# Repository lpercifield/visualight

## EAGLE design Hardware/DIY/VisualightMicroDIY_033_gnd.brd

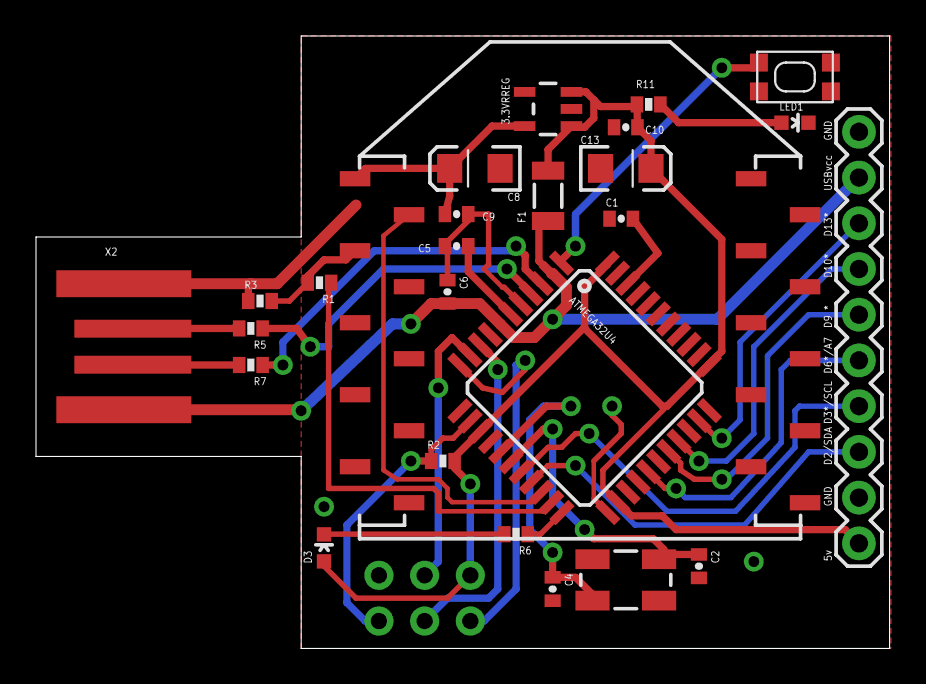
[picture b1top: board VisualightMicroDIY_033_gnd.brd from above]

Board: 2 copper layers, 47.4 x 34.0 mm, 27 parts (1 on the bottom side), 29 nets.

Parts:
3.3VRREG: MIC5219 3.3V; SOT23-5
ATMEGA32U4: ATMEGA32U4; SPARKFUN-DIGITALIC_TQFP44
C1, C9: 0.1uF; 0402-CAP
C2, C4: 22pF; 0402-CAP
C5, C6, C10: 1uF; 0402-CAP
C8, C13: 10uF; EIA3216
D3: Green; LED-0603
F1: 500mA; PTC-1206
ISP1: AVRISP-6; AVRISP
JP1: M10"; 1X10
LED1: Red; LED-0603
R1: 2.2K; 0402-RES
R2: 10K; 0402-RES
R3: 3.3K; 0402-RES
R5, R7: 22; 0402-RES
R6: 330; 0402-RES
R11: 1K; 0402-RES
SW1: SPST_TACT-KMR2; KMR2
U$1: XBEE-1B3; XBEE-SMD
X2: USBPCB; USB-A-PCB
Y1: 16MHz; CRYSTAL-SMD-5X3

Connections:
+3V3_OUT: 3.3VRREG.5, C8.A, C9.2, U$1.1
AREF: ATMEGA32U4.42, C1.2
D2: ATMEGA32U4.19, JP1.3
D3: ATMEGA32U4.18, JP1.4
D6: ATMEGA32U4.27, JP1.5
D7: ATMEGA32U4.1, SW1.3
D9: ATMEGA32U4.29, JP1.6
D10: ATMEGA32U4.30, JP1.7
D13: ATMEGA32U4.32, JP1.8
D+: ATMEGA32U4.4, R5.1
D-: ATMEGA32U4.3, R7.1
GND: 3.3VRREG.2, ATMEGA32U4.5, ATMEGA32U4.15, ATMEGA32U4.23, ATMEGA32U4.33, ATMEGA32U4.35, ATMEGA32U4.43, C1.1, C2.2, C4.2, C5.1, C6.1, C8.C, C9.1, C10.2, C13.C, ISP1.6, JP1.2, JP1.10, LED1.C, R3.1, SW1.4, U$1.10, X2.GND
MISO: ATMEGA32U4.11, ISP1.1
MOSI: ATMEGA32U4.10, ISP1.4
unnamed: ATMEGA32U4.16, C4.1, Y1.1
unnamed: ATMEGA32U4.17, C2.1, Y1.3
unnamed: ATMEGA32U4.6, C5.2
unnamed: R7.2, X2.USB_M
unnamed: D3.C, R6.2
unnamed: R5.2, X2.USB_P
unnamed: LED1.A, R11.1
RESET: ATMEGA32U4.13, ISP1.5, R2.1
SCK: ATMEGA32U4.9, ISP1.3
TX: ATMEGA32U4.21, R1.1
TXLED: ATMEGA32U4.22, R6.1
UVCC: ATMEGA32U4.2, ATMEGA32U4.7, C6.2, F1.1, JP1.9, X2.5V
VCC: 3.3VRREG.1, 3.3VRREG.3, ATMEGA32U4.14, ATMEGA32U4.24, ATMEGA32U4.34, ATMEGA32U4.44, C10.1, C13.A, D3.A, F1.2, ISP1.2, JP1.1, R2.2, R11.2
WIFIDIN: R1.2, R3.2, U$1.3
WIFIDOUT: ATMEGA32U4.20, U$1.2

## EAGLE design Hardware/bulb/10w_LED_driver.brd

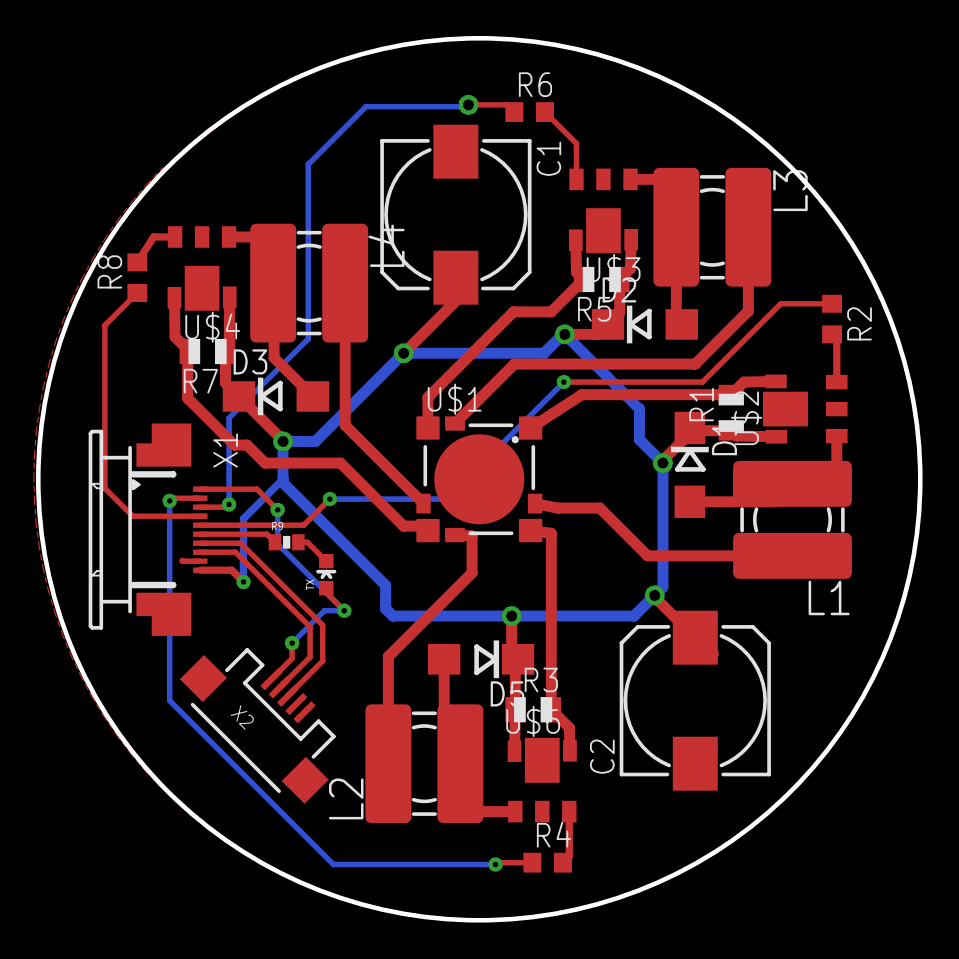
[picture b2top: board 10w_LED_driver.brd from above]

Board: 2 copper layers, 49.0 x 49.0 mm, 27 parts (0 on the bottom side), 27 nets.

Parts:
C1, C2: 150uF; 175TMP-0810
D1, D2, D3, D5: SCHOTTKY; DO214AC
L1, L2, L3, L4: 47uH; TDK6045
R1, R3, R5, R7: 0.14; R0805
R2, R4, R6, R8: 10K; R0603
R9: 330; 0402-RES
TX: Green; LED-0603
U$1: LZ4-00MD00; LZ4-00MD0
U$2, U$3, U$4, U$6: ZLED7000-LEDDRIVER; SOT89-5
X1: 52745-1090
X2: USB-MICROB

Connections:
D5: R6.1, X1.3
D9: R2.1, X1.5
D10: R8.1, X1.4
D13: R4.1, X1.2
D+IN: X1.7, X2.D+
D-IN: X1.8, X2.D-
GND: C1.-, C2.-, U$2.2, U$3.2, U$4.2, U$6.2, X1.9, X2.GND
unnamed: R2.2, U$2.3
unnamed: R9.2, TX.C
unnamed: R1.2, U$1.3, U$2.4
unnamed: L1.1, U$1.4
unnamed: D1.A, L1.2, U$2.1
unnamed: R3.2, U$1.5, U$6.4
unnamed: D5.A, L2.2, U$6.1
unnamed: R4.2, U$6.3
unnamed: R5.2, U$1.1, U$3.4
unnamed: D2.A, L3.2, U$3.1
unnamed: R6.2, U$3.3
unnamed: R7.2, U$1.7, U$4.4
unnamed: D3.A, L4.2, U$4.1
unnamed: R8.2, U$4.3
unnamed: L4.1, U$1.8
unnamed: L2.1, U$1.6
unnamed: L3.1, U$1.2
TXLED: R9.1, X1.6
UVCC: TX.A, X1.1, X2.VBUS
VCC: C1.+, C2.+, D1.C, D2.C, D3.C, D5.C, R1.1, R3.1, R5.1, R7.1, U$2.5, U$3.5, U$4.5, U$6.5, X1.10

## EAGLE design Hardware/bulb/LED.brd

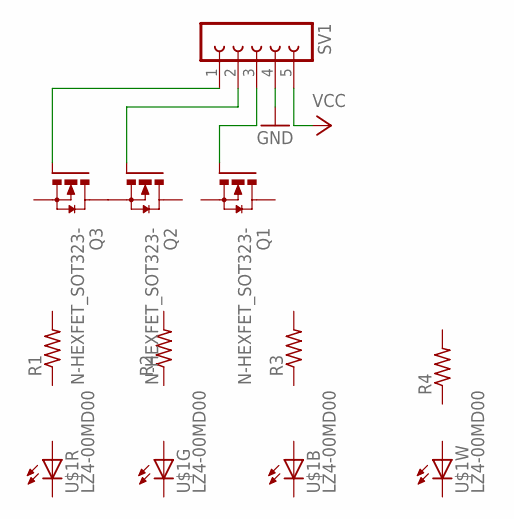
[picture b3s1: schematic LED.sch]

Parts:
Q1, Q2, Q3: N-HEXFET_SOT323-; SOT223
R1, R2, R3, R4: R-US_0204/7; 0204/7
SV1: FE05-1
U$1: LZ4-00MD00; LZ4-00MD0

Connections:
GND: SV1.4
unnamed: Q2.3 (S), Q3.4 (D)
unnamed: Q3.1 (G), SV1.1
unnamed: Q2.1 (G), SV1.2
unnamed: Q1.1 (G), SV1.3
VCC: SV1.5

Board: 2 copper layers, 9 parts (0 on the bottom side), 4 nets, no tracks yet.

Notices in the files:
parts and their libraries:
SparkFun-DigitalIC: Licensing: CC v3.0 Share-Alike You are welcome to use this library for commercial purposes.
